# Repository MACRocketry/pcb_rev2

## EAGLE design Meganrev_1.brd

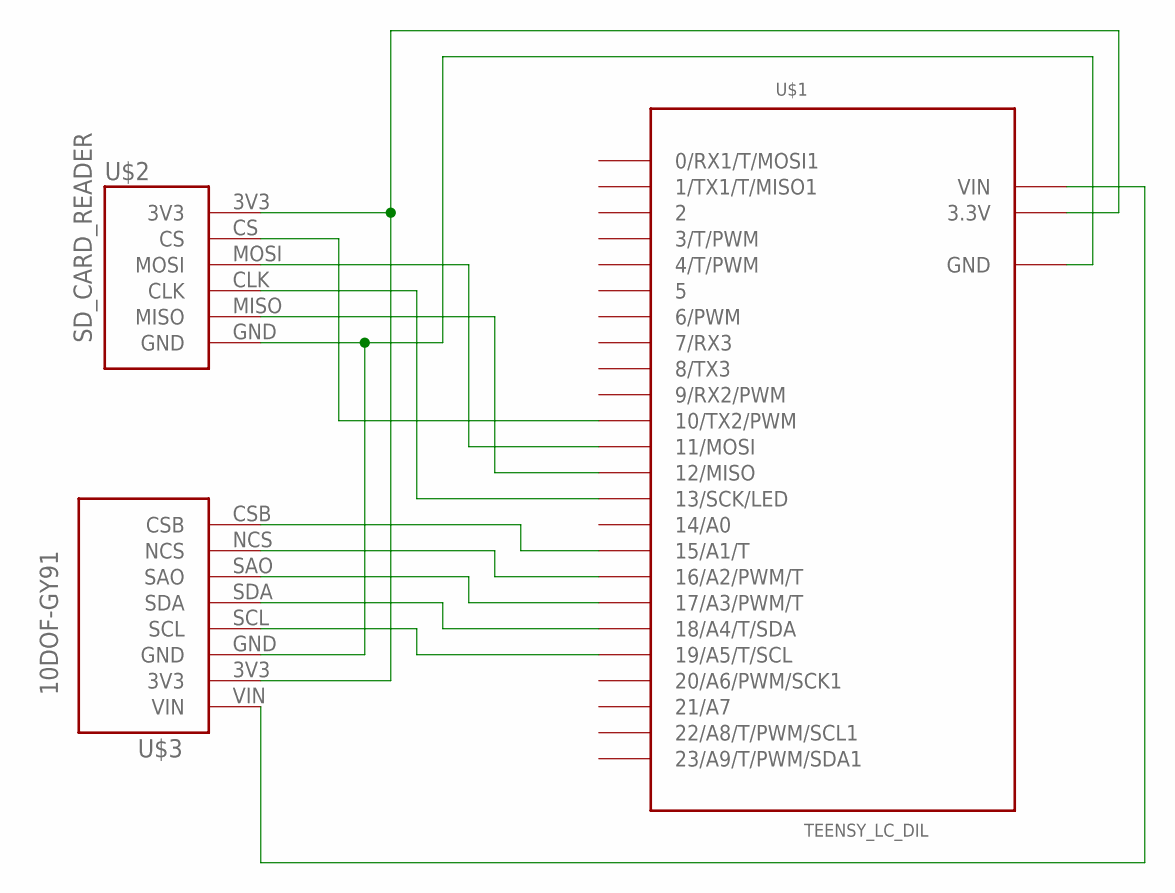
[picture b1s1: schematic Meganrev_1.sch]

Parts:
U$1: TEENSY_LC_DIL; TEENSY_3.0-3.2&LC_DIL
U$2: SD_CARD_READER; MICRO_SD_READER_3V3
U$3: 10DOF-GY91; 10DOF-GY-91

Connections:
unnamed: U$1.19/A5 (19/A5/T/SCL), U$3.SCL
unnamed: U$1.AGND (GND), U$1.GND, U$2.GND, U$3.GND
unnamed: U$1.12 (12/MISO), U$2.MISO
unnamed: U$1.11 (11/MOSI), U$2.MOSI
unnamed: U$1.13 (13/SCK/LED), U$2.CLK
unnamed: U$1.VIN, U$3.VIN
unnamed: U$1.18/A4 (18/A4/T/SDA), U$3.SDA
unnamed: U$1.17/A3 (17/A3/PWM/T), U$3.SAO
unnamed: U$1.16/A2 (16/A2/PWM/T), U$3.NCS
unnamed: U$1.10 (10/TX2/PWM), U$2.CS
unnamed: U$1.15/A1 (15/A1/T), U$3.CSB
unnamed: U$1.3.3V, U$2.3V3, U$3.3V3

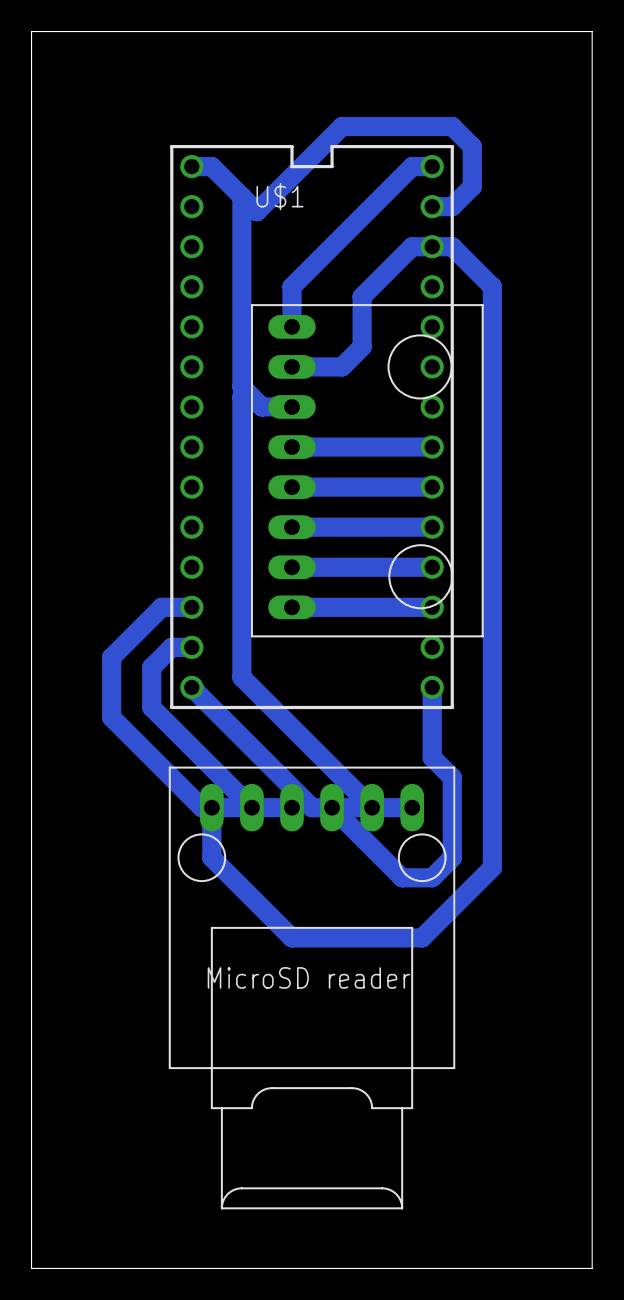
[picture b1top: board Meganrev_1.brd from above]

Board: 2 copper layers, 35.5 x 78.4 mm, 3 parts (0 on the bottom side), 12 nets.

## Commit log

2020-02-08 init git version control
2020-03-01 create new branch for Megan's PCB
2020-03-07 update GY-91 nameing to 10DOF-GY-91
